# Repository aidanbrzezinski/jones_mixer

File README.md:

<h1 align="center">JONES_MIXER</h1>
<p align="center">Jones Mixer</p>
<p align="center"><em>Simple Jones Mixer.</em></p>

<p align="center" width="100%">
  
</p>

***

<p align="center">
  
&nbsp; &nbsp; &nbsp; &nbsp;
  
</p>

***

## SPECIFICATIONS

| Parameter | Value |
| --- | --- |
| Dimensions | 32.0 × 32.0 mm |
| Company | LTU |
| Designer | A.B., C.B., A.V. |
| Revision | 1.0.2 |

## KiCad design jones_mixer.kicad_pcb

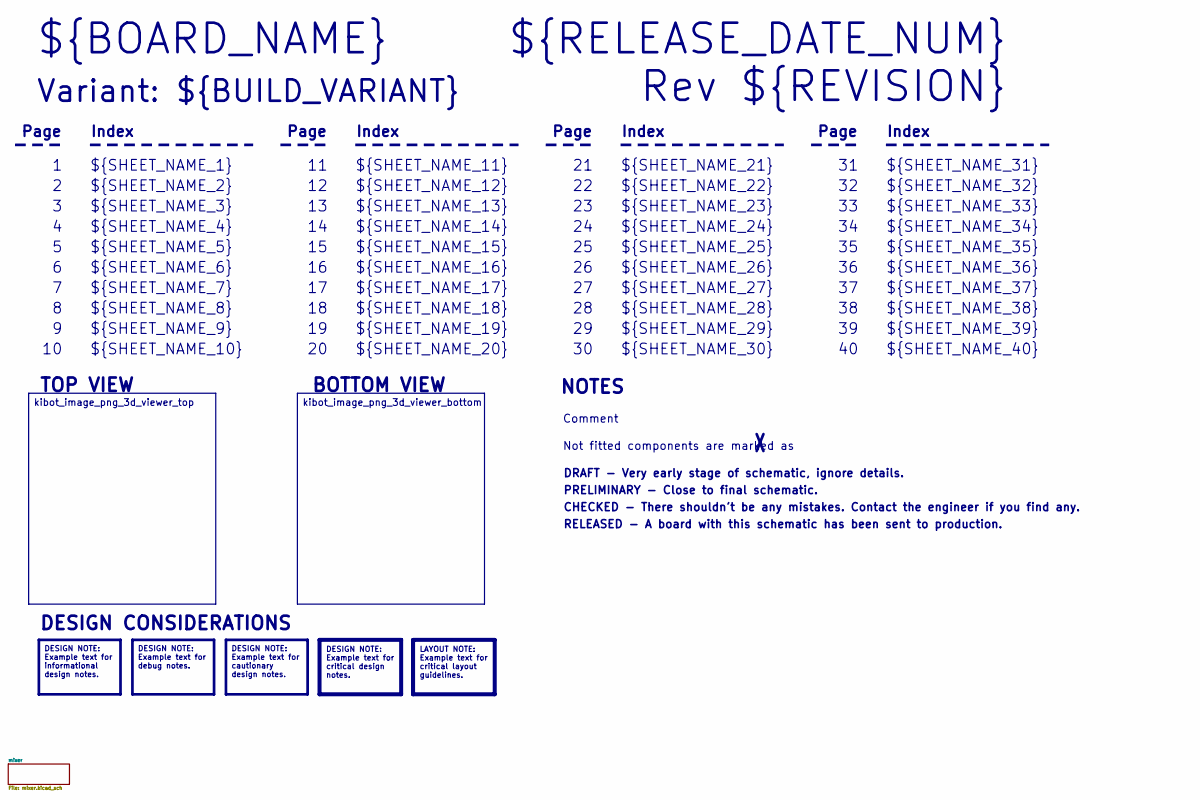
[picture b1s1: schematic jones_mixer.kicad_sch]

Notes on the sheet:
Variant: ${BUILD_VARIANT}
RELEASED - A board with this schematic has been sent to production.
${SHEET_NAME_24}
Index
Page
PRELIMINARY - Close to final schematic.
${SHEET_NAME_22}
DRAFT - Very early stage of schematic, ignore details.
${SHEET_NAME_12}
${SHEET_NAME_8}
${SHEET_NAME_2}
${SHEET_NAME_5}
${SHEET_NAME_20}
${SHEET_NAME_23}
${RELEASE_DATE_NUM}
${SHEET_NAME_35}
Not fitted components are marked as
${SHEET_NAME_11}
${SHEET_NAME_6}
${SHEET_NAME_37}
${SHEET_NAME_26}
${SHEET_NAME_36}
Rev ${REVISION}
${SHEET_NAME_15}
CHECKED - There shouldn't be any mistakes. Contact the engineer if you find any.
BOTTOM VIEW
${SHEET_NAME_14}
${SHEET_NAME_21}
${SHEET_NAME_17}
${SHEET_NAME_18}
${SHEET_NAME_7}
${SHEET_NAME_31}
${BOARD_NAME}
NOTES
${SHEET_NAME_40}
${SHEET_NAME_39}
${SHEET_NAME_32}
${SHEET_NAME_1}
${SHEET_NAME_9}
${SHEET_NAME_38}

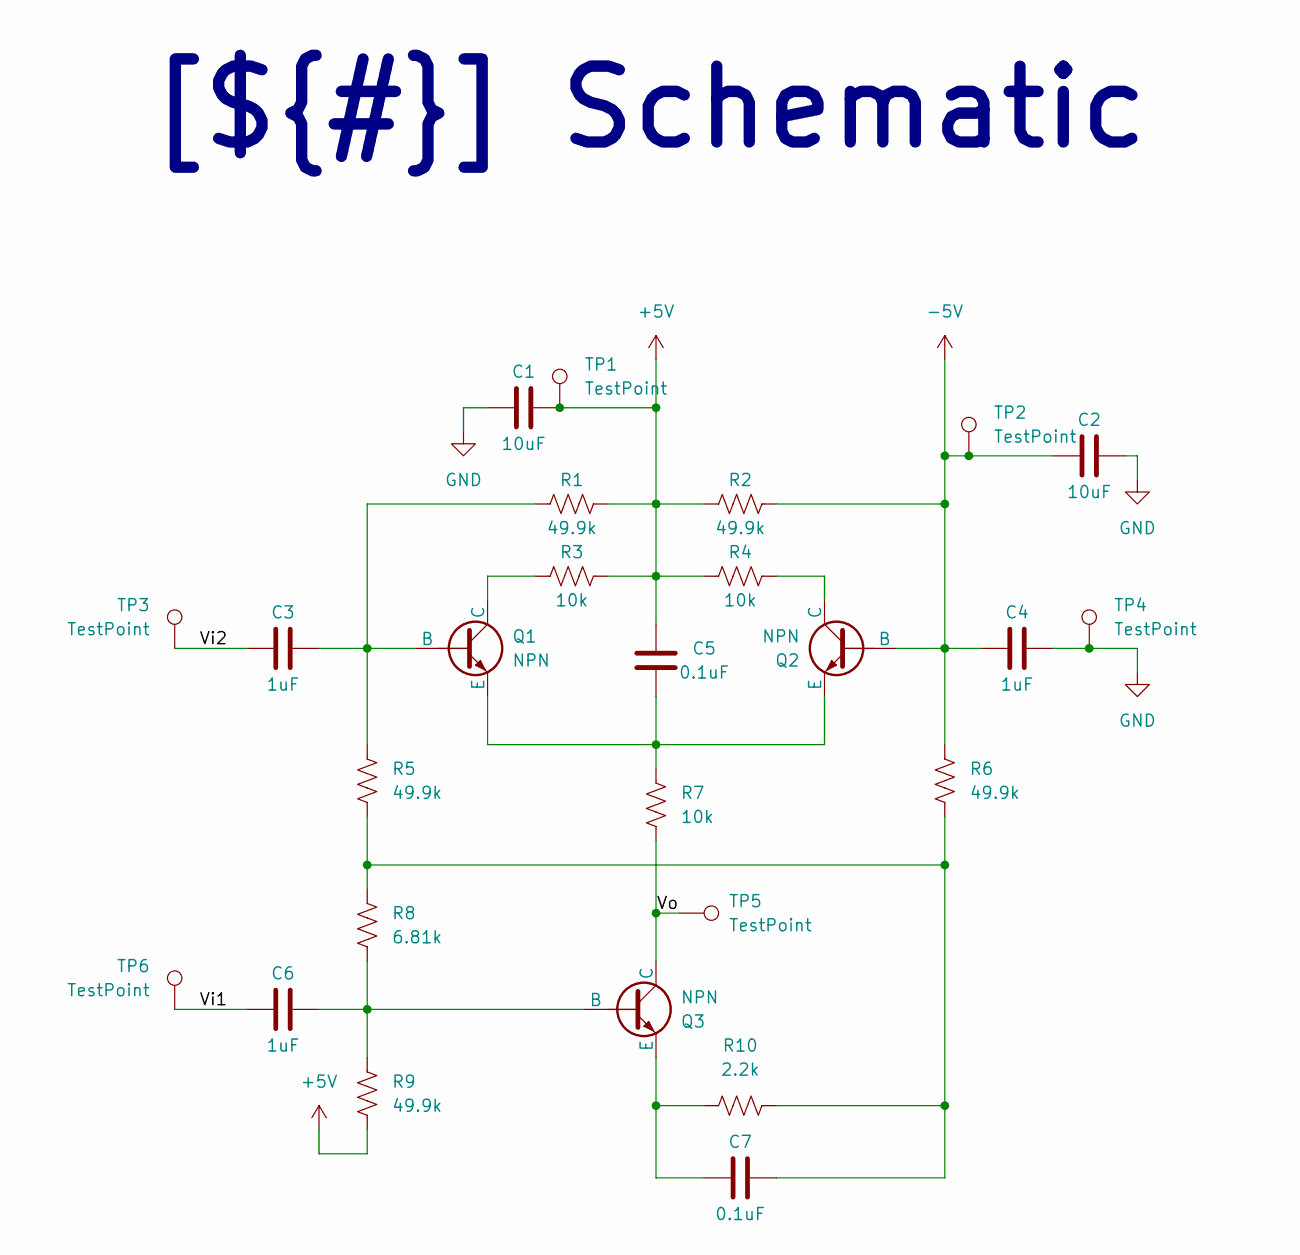
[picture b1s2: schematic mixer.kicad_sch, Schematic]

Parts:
C1, C2: 10uF; C_0603_1608Metric; MPN CL10A106MA8NRNC
C3, C4, C6: 1uF; C_0603_1608Metric; MPN C0603C105K3RACTU
C5, C7: 0.1uF; C_0603_1608Metric; MPN CC0603KRX7R9BB104
Q1, Q2, Q3: NPN; SOT-23-3; MPN MMBT3904LT1G
R1, R2, R5, R6, R9: 49.9k; R_0603_1608Metric; MPN AF0603FR-0749K9L
R3, R4, R7: 10k; R_0603_1608Metric; MPN AC0603FR-0710KL
R8: 6.81k; R_0603_1608Metric; MPN ERJ-3EKF6811V
R10: 2.2k; R_0603_1608Metric; MPN RC0603FR-072K2L
TP1, TP2: TestPoint; TestPoint_Keystone_5010
TP3, TP5, TP6: TestPoint; TestPoint_Keystone_5012
TP4: TestPoint; TestPoint_Keystone_5011

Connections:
/mixer/+5V: C1.2, C5.2, R1.1, R2.1, R3.2, R4.1, R9.2, TP1.1 (1_1)
/mixer/-5V: C2.1, C4.1, Q2.2 (B), R2.2, R6.2, TP2.1 (1_1)
/mixer/GND: C1.1, C2.2, C4.2, TP4.1 (1_1)
/mixer/Vi1: C6.1, TP6.1 (1_1)
/mixer/Vi2: C3.1, TP3.1 (1_1)
/mixer/Vo: Q3.1 (C), R7.1, TP5.1 (1_1)
unnamed: C7.2, R5.2, R6.1, R8.2, R10.1
unnamed: C3.2, Q1.2 (B), R1.2, R5.1
unnamed: Q1.1 (C), R3.1
unnamed: C5.1, Q1.3 (E), Q2.3 (E), R7.2
unnamed: Q2.1 (C), R4.2
unnamed: C6.2, Q3.2 (B), R8.1, R9.1
unnamed: C7.1, Q3.3 (E), R10.2

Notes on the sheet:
[${#}] ${TITLE}

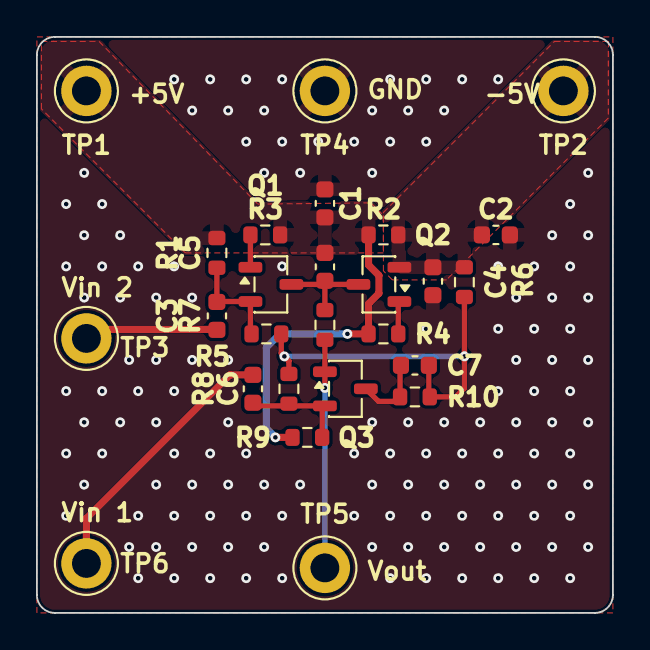
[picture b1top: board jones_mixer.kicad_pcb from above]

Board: 2 copper layers, 32.0 x 32.0 mm, 26 parts (0 on the bottom side), 13 nets.
